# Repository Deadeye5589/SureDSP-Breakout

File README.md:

# SureDSP-Breakout
Breakout Board for SureDSP to adapt China Modules

This project won't be supportet in any way, but on the other hand it can be used in any way you like.<br>
The creator of this project won't be responsible for any trouble, harm or deadly incidents that should occure while using this project data, parts of the project or complete boards.<br>
Now for the fun part.<br><br>

This breakout board includes an automotive qualified power supply with a quiescent current of >2µA. <br>
The DC/DC converter can supply the DSP down to an input voltage of 6V and is therefore suitable for start/stop systems.<br><br>

The modules can be purchased at the common Chinese webshops like Aliexpress<br><br>

The default configuration can support up to:<br>
4x DAC output via PCM5102 chipset 2,98€ per piece<br>
4x Analog output directly from SureDSP<br>
1x APTx Bluetooth receiver via CSR64215 chipset 8,08€<br>
1x SPDIF input via DIR9001 chipset 11,20€<br>
2x ADC input via PCM1808 Chipsatz 3,12€ per piece<br>
2x Analog Input from SureDSP<br>
1x Debugger 2,92€<br><br>

The PCB is the size of 160x100 mm and a 2 layer design.<br>
Drill holes are 0,8mm or 1,0mm<br>
The PCB can be etched with iron III chloride in a spray booth. <br>
It is possible to manufacture the PCB with tools avaiable to makers.<br>
But don't take on this project if you don't feel like you can do it by your own. <br>
You will not get any support.<br>

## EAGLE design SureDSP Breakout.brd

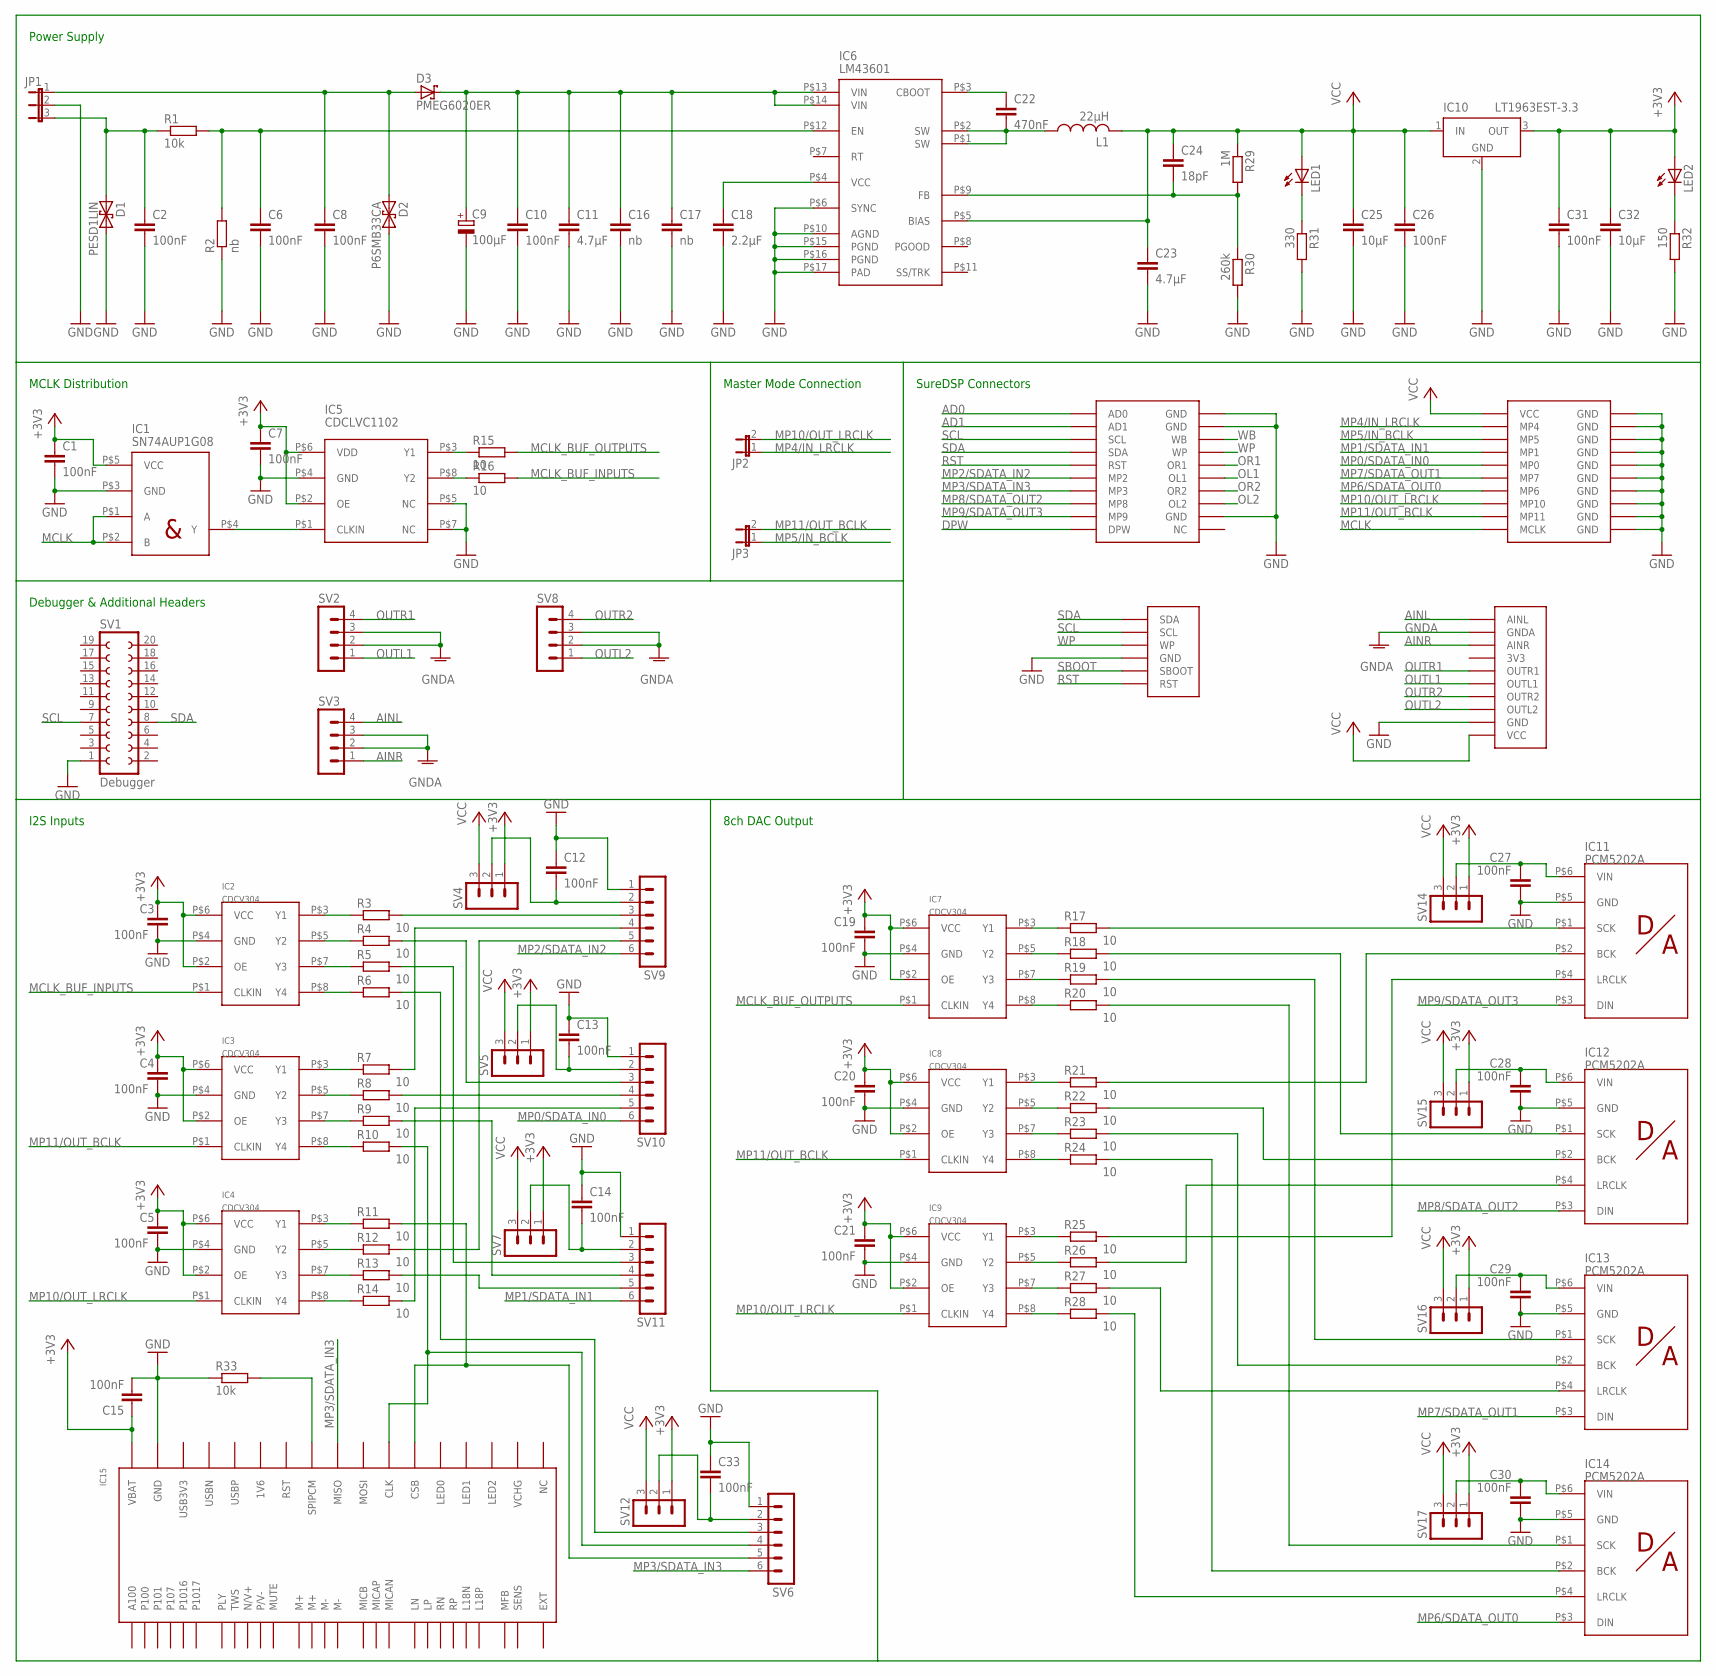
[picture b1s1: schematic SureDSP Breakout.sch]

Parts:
C1, C3, C4, C5, C7, C12, C13, C14, C15, C19, C20, C21, C26, C27, C28, C29, C30, C31, C33: 100nF; C0805K
C2, C6, C8, C10: 100nF; C1210K
C9: 100µF; 150CLZ-0810
C11: 4.7µF; C1210K
C16, C17: nb; C1210K
C18: 2.2µF; C0805K
C22: 470nF; C0805K
C23: 4.7µF; C0805K
C24: 18pF; C0805K
C25, C32: 10µF; C1210K
D1: PESD1LIN
D2: P6SMB33CA; P6SMB
D3: PMEG6020ER
IC1: SN74AUP1G08
IC2, IC3, IC4, IC7, IC8, IC9: CDCV304
IC5: CDCLVC1102
IC6: LM43601
IC10: LT1963EST-3.3; SOT223
IC11, IC12, IC13, IC14: PCM5202A
IC15: CSRA64215
IC16: SUREDSP
JP1: JP2E; JP2
JP2, JP3: JP1E; JP1
L1: 22µH; L5650M
LED1, LED2: LEDSML0805; SML0805
R1, R33: 10k; R2012
R2: nb; R2012
R3, R4, R5, R6, R7, R8, R9, R10, R11, R12, R13, R14, R15, R16, R17, R18, R19, R20, R21, R22, R23, R24, R25, R26, R27, R28: 10; R2012
R29: 1M; R2012
R30: 260k; R2012
R31: 330; R2012
R32: 150; R2012
SV1: Debugger; FE10-2
SV2, SV3, SV8: MA04-1
SV4, SV5, SV7, SV12, SV14, SV15, SV16, SV17: MA03-1
SV6, SV9, SV10, SV11: MA06-1

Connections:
+3V3: C1.1, C3.1, C4.1, C5.1, C7.1, C15.1, C19.1, C20.1, C21.1, C31.1, C32.1, IC1.P$5 (VCC), IC2.P$2 (OE), IC2.P$6 (VCC), IC3.P$2 (OE), IC3.P$6 (VCC), IC4.P$2 (OE), IC4.P$6 (VCC), IC5.P$2 (OE), IC5.P$6 (VDD), IC7.P$2 (OE), IC7.P$6 (VCC), IC8.P$2 (OE), IC8.P$6 (VCC), IC9.P$2 (OE), IC9.P$6 (VCC), IC10.3 (OUT), IC15.P$5 (VBAT), LED2.A, SV4.1, SV5.1, SV7.1, SV12.1, SV14.1, SV15.1, SV16.1, SV17.1
AD0: IC16.AD0
AD1: IC16.AD1
AINL: IC16.AINL, SV3.4
AINR: IC16.AINR, SV3.1
DPW: IC16.DPW
GND: C1.2, C2.2, C3.2, C4.2, C5.2, C6.2, C7.2, C8.2, C9.-, C10.2, C11.2, C12.1, C13.1, C14.1, C15.2, C16.2, C17.2, C18.2, C19.2, C20.2, C21.2, C23.2, C25.2, C26.2, C27.2, C28.2, C29.2, C30.2, C31.2, C32.2, C33.1, D1.P$2 (2), D2.P$2 (2), IC1.P$3 (GND), IC2.P$4 (GND), IC3.P$4 (GND), IC4.P$4 (GND), IC5.P$4 (GND), IC5.P$5 (NC), IC5.P$7 (NC), IC6.P$6 (SYNC), IC6.P$10 (AGND), IC6.P$15 (PGND), IC6.P$16 (PGND), IC6.P$17 (PAD), IC7.P$4 (GND), IC8.P$4 (GND), IC9.P$4 (GND), IC10.2 (GND), IC10.4 (GND), IC11.P$5 (GND), IC12.P$5 (GND), IC13.P$5 (GND), IC14.P$5 (GND), IC15.P$6 (GND), IC16.GND6ER (GND), IC16.GND10ER (GND), IC16.GND20ER (GND), IC16.GND20ER1 (GND), IC16.GND20ER2 (GND), IC16.P$2 (GND), IC16.P$3 (GND), IC16.P$6 (GND), IC16.P$8 (GND), IC16.P$10 (GND), IC16.P$12 (GND), IC16.P$14 (GND), IC16.P$16 (GND), IC16.P$18 (GND), IC16.P$55 (GND), JP1.2, R2.1, R30.2, R31.2, R32.2, R33.1, SV1.1, SV6.1, SV9.1, SV10.1, SV11.1
GNDA: IC16.AGND (GNDA), SV2.2, SV2.3, SV3.2, SV3.3, SV8.2, SV8.3
MCLK: IC1.P$1 (A), IC1.P$2 (B), IC16.MCLK
MCLK_BUF_INPUTS: IC2.P$1 (CLKIN), R16.2
MCLK_BUF_OUTPUTS: IC7.P$1 (CLKIN), R15.2
MP0/SDATA_IN0: IC16.MP0, SV10.6
MP1/SDATA_IN1: IC16.MP1, SV11.6
MP2/SDATA_IN2: IC16.MP2, SV9.6
MP3/SDATA_IN3: IC15.P$7 (MISO), IC16.MP3, SV6.6
MP4/IN_LRCLK: IC16.MP4, JP2.1
MP5/IN_BCLK: IC16.MP5, JP3.1
MP6/SDATA_OUT0: IC14.P$3 (DIN), IC16.MP6
MP7/SDATA_OUT1: IC13.P$3 (DIN), IC16.MP7
MP8/SDATA_OUT2: IC12.P$3 (DIN), IC16.MP8
MP9/SDATA_OUT3: IC11.P$3 (DIN), IC16.MP9
MP10/OUT_LRCLK: IC4.P$1 (CLKIN), IC9.P$1 (CLKIN), IC16.MP10, JP2.2
MP11/OUT_BCLK: IC3.P$1 (CLKIN), IC8.P$1 (CLKIN), IC16.MP11, JP3.2
unnamed: IC7.P$3 (Y1), R17.1
unnamed: IC12.P$1 (SCK), R18.2
unnamed: IC13.P$1 (SCK), R19.2
unnamed: IC14.P$1 (SCK), R20.2
unnamed: IC14.P$2 (BCK), R24.2
unnamed: IC14.P$4 (LRCLK), R28.2
unnamed: IC13.P$4 (LRCLK), R27.2
unnamed: IC13.P$2 (BCK), R23.2
unnamed: IC12.P$4 (LRCLK), R26.2
unnamed: IC12.P$2 (BCK), R22.2
unnamed: IC11.P$4 (LRCLK), R25.2
unnamed: IC11.P$2 (BCK), R21.2
unnamed: IC7.P$5 (Y2), R18.1
unnamed: IC7.P$7 (Y3), R19.1
unnamed: IC7.P$8 (Y4), R20.1
unnamed: IC8.P$3 (Y1), R21.1
unnamed: IC8.P$5 (Y2), R22.1
unnamed: IC8.P$7 (Y3), R23.1
unnamed: IC8.P$8 (Y4), R24.1
unnamed: IC9.P$3 (Y1), R25.1
unnamed: IC9.P$5 (Y2), R26.1
unnamed: IC9.P$7 (Y3), R27.1
unnamed: IC9.P$8 (Y4), R28.1
unnamed: IC11.P$1 (SCK), R17.2
unnamed: R3.2, SV9.3
unnamed: IC1.P$4 (Y), IC5.P$1 (CLKIN)
unnamed: IC5.P$3 (Y1), R15.1
unnamed: IC5.P$8 (Y2), R16.1
unnamed: R7.2, SV9.4
unnamed: R12.2, SV9.5
unnamed: R4.2, SV10.3
unnamed: R5.2, SV11.3
unnamed: C12.2, SV4.2, SV9.2
unnamed: R8.2, SV10.4
unnamed: R9.2, SV11.4
unnamed: C14.2, SV7.2, SV11.2
unnamed: R14.2, SV10.5
unnamed: R13.2, SV11.5
unnamed: IC2.P$3 (Y1), R3.1
unnamed: IC2.P$5 (Y2), R4.1
unnamed: IC2.P$7 (Y3), R5.1
unnamed: IC2.P$8 (Y4), R6.1
unnamed: IC3.P$3 (Y1), R7.1
unnamed: IC3.P$5 (Y2), R8.1
unnamed: IC3.P$7 (Y3), R9.1
unnamed: IC3.P$8 (Y4), R10.1
unnamed: IC4.P$3 (Y1), R11.1
unnamed: IC4.P$5 (Y2), R12.1
unnamed: IC4.P$7 (Y3), R13.1
unnamed: IC4.P$8 (Y4), R14.1
unnamed: C33.2, SV6.2, SV12.2
unnamed: C18.1, IC6.P$4 (VCC)
unnamed: C9.+, C10.1, C11.1, C16.1, C17.1, D3.P$2 (C), IC6.P$13 (VIN), IC6.P$14 (VIN)
unnamed: C22.2, IC6.P$1 (SW), IC6.P$2 (SW), L1.1
unnamed: C22.1, IC6.P$3 (CBOOT)
unnamed: C2.1, D1.P$1 (1), JP1.3, R1.1
unnamed: C8.1, D2.P$1 (1), D3.P$1 (A), JP1.1
unnamed: C24.2, IC6.P$9 (FB), R29.2, R30.1
unnamed: C6.1, IC6.P$12 (EN), R1.2, R2.2
unnamed: C30.1, IC14.P$6 (VIN), SV17.2
unnamed: C29.1, IC13.P$6 (VIN), SV16.2
unnamed: C28.1, IC12.P$6 (VIN), SV15.2
unnamed: C27.1, IC11.P$6 (VIN), SV14.2
unnamed: C13.2, SV5.2, SV10.2
unnamed: IC15.P$11 (SPIPCM), R33.2
unnamed: LED2.C, R32.1
unnamed: LED1.C, R31.1
unnamed: R6.2, SV6.3
unnamed: IC15.P$9 (CLK), R10.2, SV6.4
unnamed: IC15.P$10 (CSB), R11.2, SV6.5
OL1: IC16.OL1
OL2: IC16.OL2
OR1: IC16.OR1
OR2: IC16.OR2
OUTL1: IC16.OUTL1, SV2.1
OUTL2: IC16.OUTL2, SV8.1
OUTR1: IC16.OUTR1, SV2.4
OUTR2: IC16.OUTR2, SV8.4
RST: IC16.RESET (RST), IC16.RST
SBOOT: IC16.SBOOT
SCL: IC16.SCL, IC16.SCL20ER (SCL), SV1.7
SDA: IC16.SDA, IC16.SDA20ER (SDA), SV1.8
VCC: C23.1, C24.1, C25.1, C26.1, IC6.P$5 (BIAS), IC10.1 (IN), IC16.VIN10ER (VCC), IC16.VIN@2 (VCC), L1.2, LED1.A, R29.1, SV4.3, SV5.3, SV7.3, SV12.3, SV14.3, SV15.3, SV16.3, SV17.3
WB: IC16.WB
WP: IC16.WP, IC16.WP20ER (WP)

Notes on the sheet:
SureDSP Connectors
8ch DAC Output
Master Mode Connection
MCLK Distribution
Debugger & Additional Headers
I2S Inputs
Power Supply

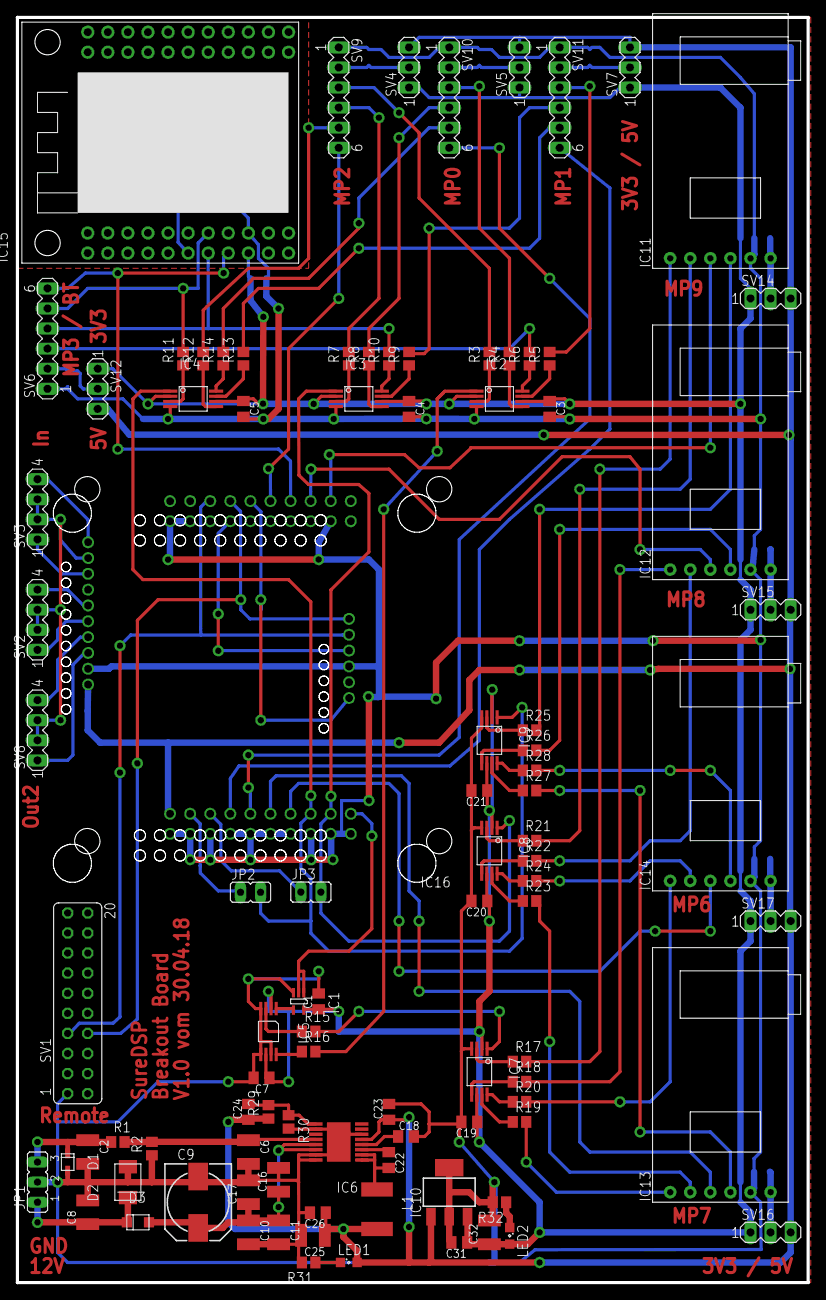
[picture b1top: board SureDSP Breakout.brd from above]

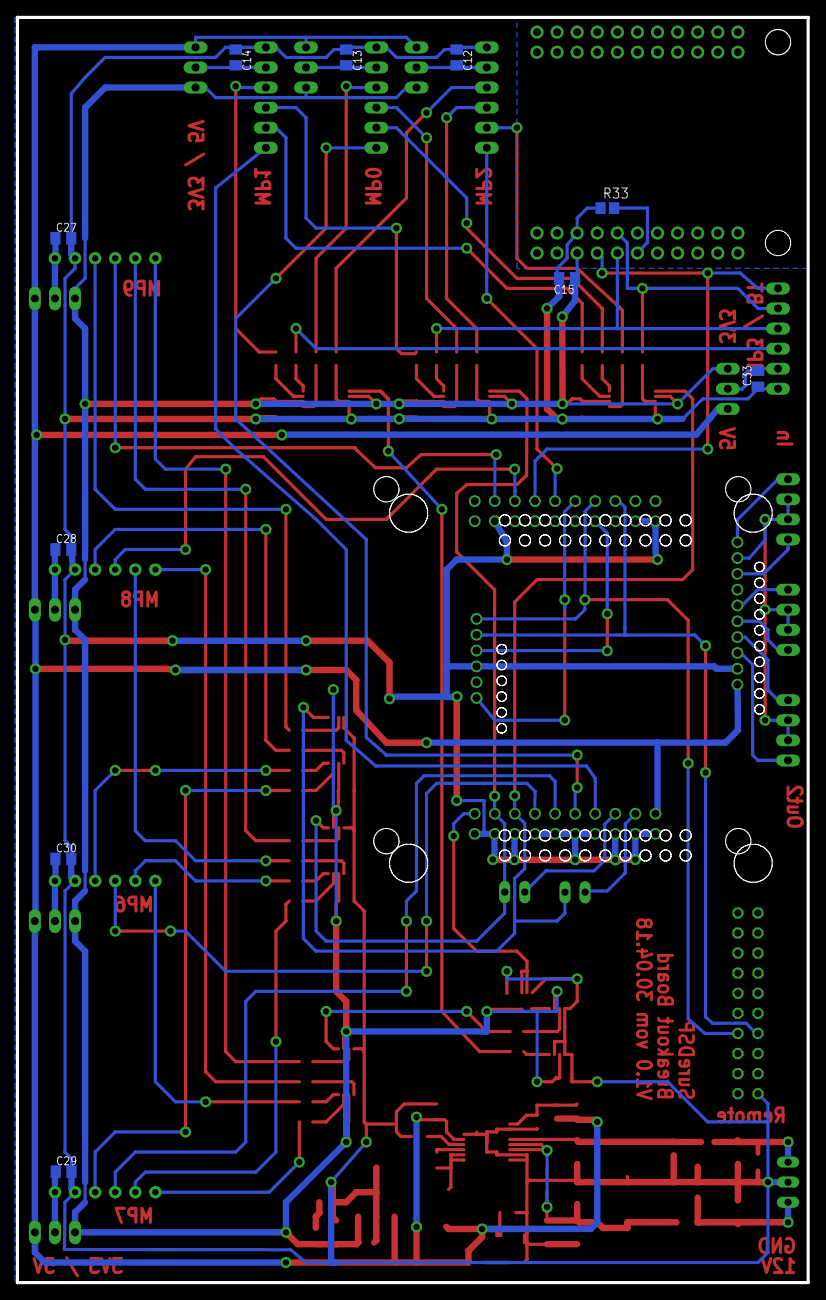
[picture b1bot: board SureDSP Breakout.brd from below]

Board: 2 copper layers, 100.0 x 160.0 mm, 107 parts (10 on the bottom side), 99 nets.

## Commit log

2019-04-26 PDF Plots of Eagle Layouts
